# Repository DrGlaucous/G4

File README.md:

# "Governor" G4

This is a repo for a low-cost and feature-rich "flywheel-type" nerf blaster.

Features/Speficications:
- Goal build cost < 150$
- Minimal plastic-anchored screws *(almost evertthing is secured with bolts + captive nuts)*
- Brushless motor flyhweels
- Solenoid pusher
- LCD display
- Angled talon compatability *(straight stick support planned)*
- Integrated ammo counter hardware
- Integrated chronograph hardware
- 3-5S Lipo compatable
- 6cm flywheel diameter
- ESP32 controller
- Closed-loop flywheel control (providing fixed RPM and fast spinup times)
- Through-hole electronics and soldering
- Fast decay solenoid driver

Many of these features are implemented in the G4's companion firmware, [Detty](https://github.com/DrGlaucous/DettyFW).

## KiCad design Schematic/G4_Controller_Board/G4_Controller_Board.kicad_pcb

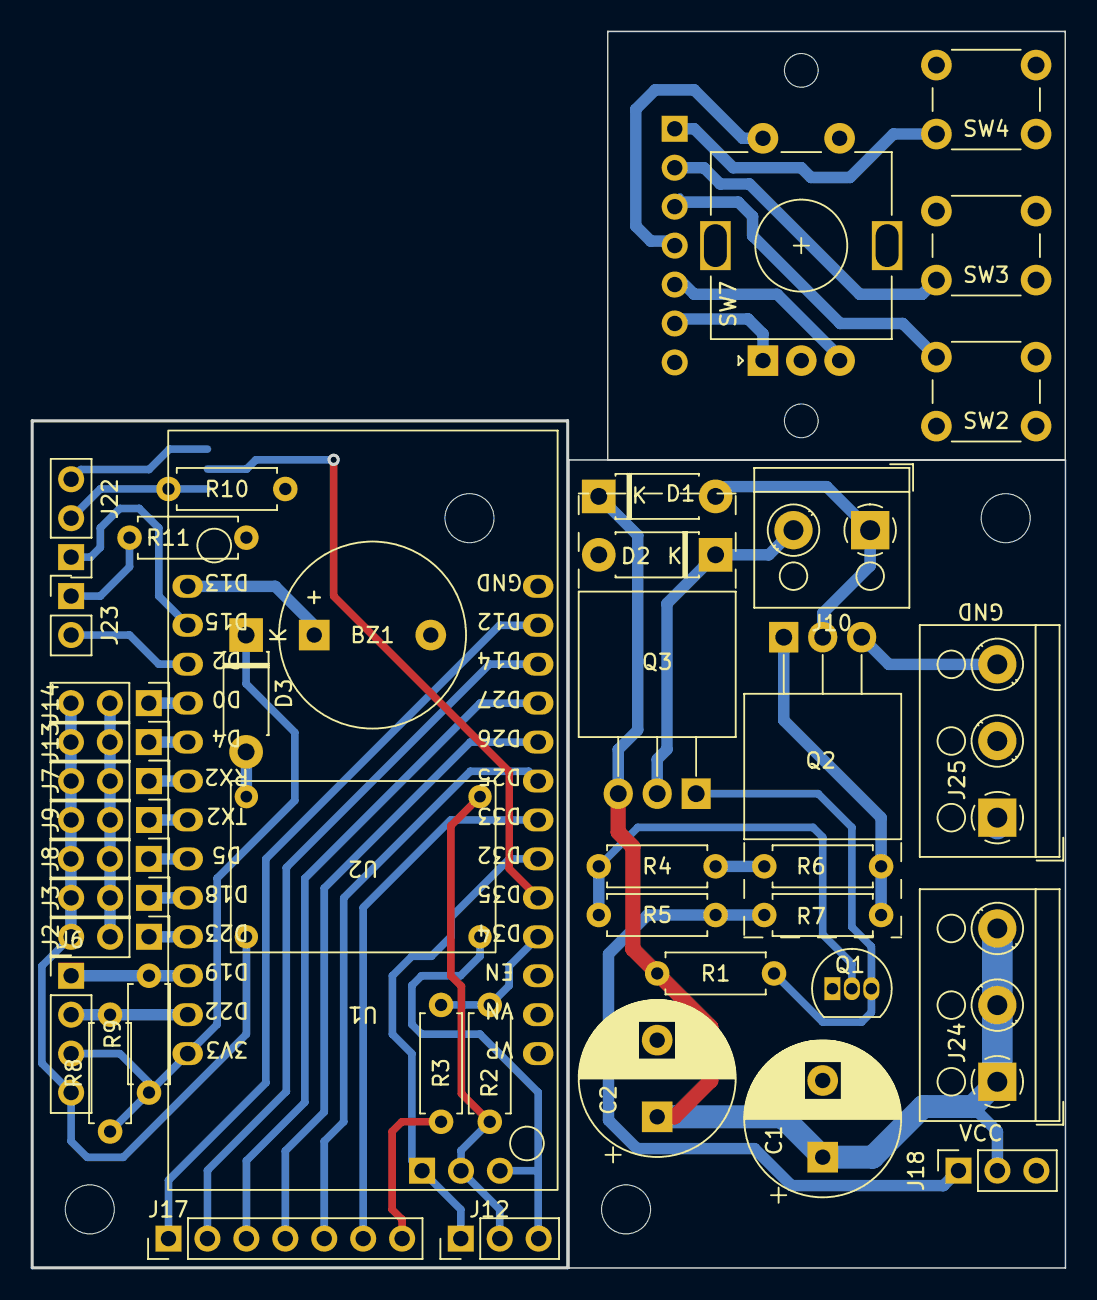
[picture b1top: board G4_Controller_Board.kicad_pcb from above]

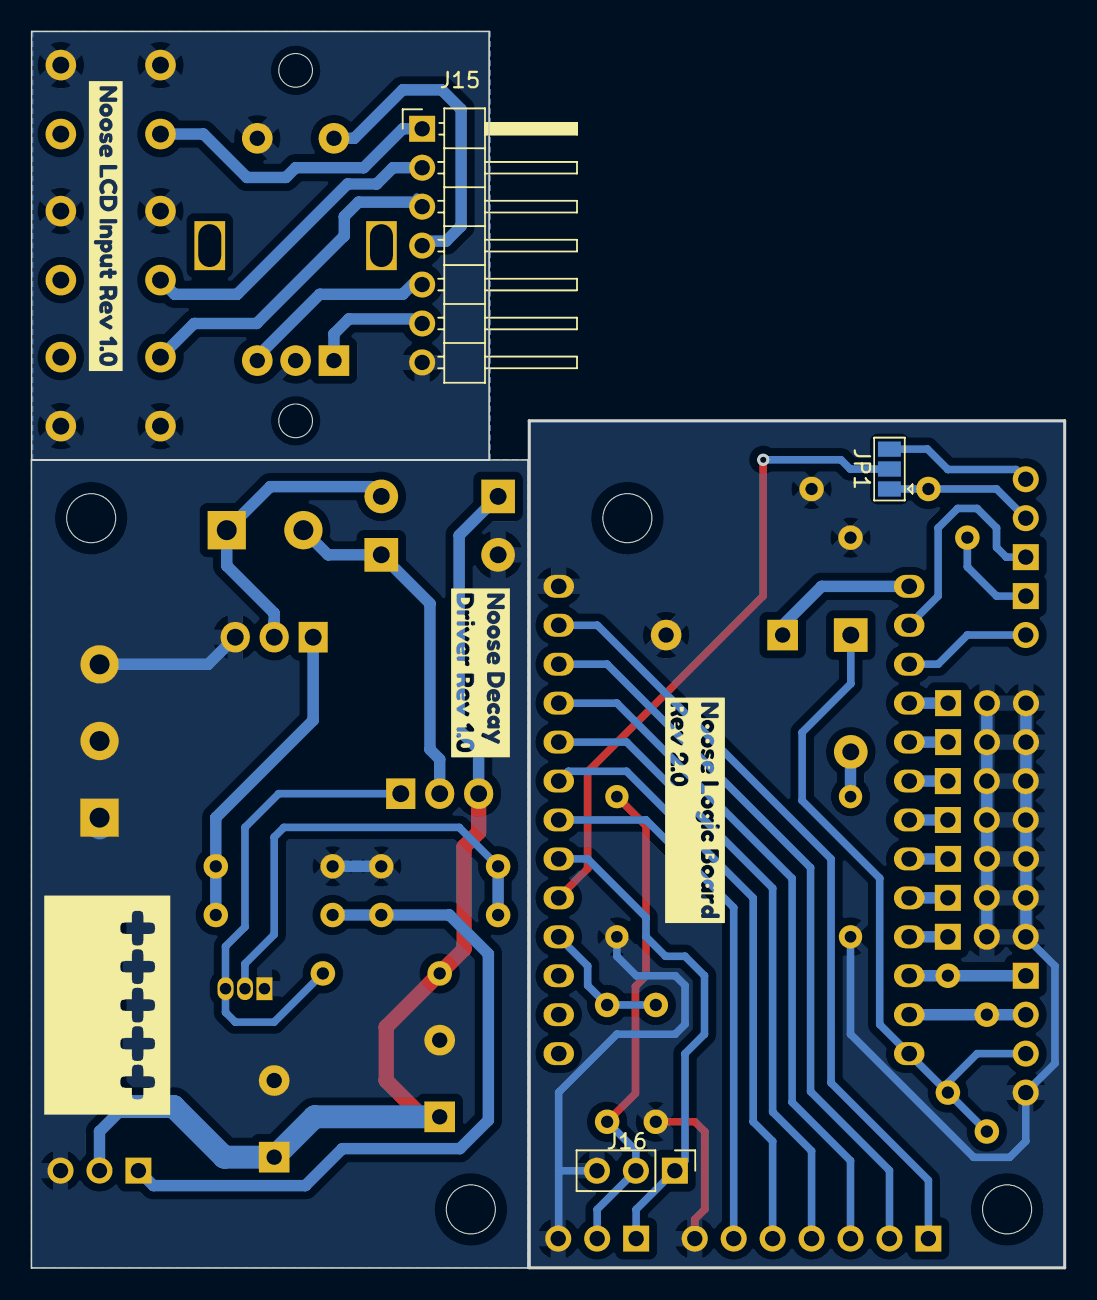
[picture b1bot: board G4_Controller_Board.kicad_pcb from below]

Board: 2 copper layers, 67.3 x 80.6 mm, 55 parts (7 on the bottom side), 33 nets.

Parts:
BZ1: Buzzer; Buzzer_12x9.5RM7.6
C1, C2: 470uF; CP_Radial_D10.0mm_P5.00mm
D1, D2, D3: 1N4001; D_DO-41_SOD81_P7.62mm_Horizontal
H1, H1#2, H1#3, H1#4: MountingHole; MountingHole_3.2mm_M3
H1#5, H1#6: MountingHole; MountingHole_2.2mm_M2
J2: ESC Right; PinHeader_1x03_P2.54mm_Vertical
J3: ESC Left; PinHeader_1x03_P2.54mm_Vertical
J6: I2C Out; PinHeader_1x04_P2.54mm_Vertical
J7: Rev Trigger (Optional); PinHeader_1x03_P2.54mm_Vertical
J8: Fire Trigger; PinHeader_1x03_P2.54mm_Vertical
J9: Magazine Removal Trigger; PinHeader_1x03_P2.54mm_Vertical
J10: Solenoid; TerminalBlock_RND_205-00001_1x02_P5.00mm_Horizontal
J12, J16: Board Interconnect; PinHeader_1x03_P2.54mm_Vertical
J13: SolenoidTrig A (Optional); PinHeader_1x03_P2.54mm_Vertical
J14: SolenoidTrig B (Optional); PinHeader_1x03_P2.54mm_Vertical
J15: Board Interconnect; PinHeader_1x07_P2.54mm_Horizontal
J17: Board Interconnect; PinHeader_1x07_P2.54mm_Vertical
J18: Board Interconnect; PinSocket_1x03_P2.54mm_Vertical
J22: IR LED Rec.; PinHeader_1x03_P2.54mm_Vertical
J23: IR LED Emitter; PinHeader_1x02_P2.54mm_Vertical
J24: Positive BUS; TerminalBlock_RND_205-00002_1x03_P5.00mm_Horizontal
J25: Negative BUS; TerminalBlock_RND_205-00002_1x03_P5.00mm_Horizontal
JP1: Jumper_3_Bridged12; SolderJumper-3_P1.3mm_Open_Pad1.0x1.5mm
Q1: 2N7000; TO-92_Inline
Q2: Q_NMOS_GDS; TO-220-3_Horizontal_TabUp
Q3: Q_PMOS_GDS; TO-220-3_Horizontal_TabUp
R1, R4, R6: 10KR; R_Axial_DIN0207_L6.3mm_D2.5mm_P7.62mm_Horizontal
R2: 150k Ohm; R_Axial_DIN0207_L6.3mm_D2.5mm_P7.62mm_Horizontal
R3: 10k Ohm; R_Axial_DIN0207_L6.3mm_D2.5mm_P7.62mm_Horizontal
R5, R7: 100R; R_Axial_DIN0207_L6.3mm_D2.5mm_P7.62mm_Horizontal
R8, R9: 2.4k Ohm; R_Axial_DIN0207_L6.3mm_D2.5mm_P7.62mm_Horizontal
R10: 10K Ohm; R_Axial_DIN0207_L6.3mm_D2.5mm_P7.62mm_Horizontal
R11: 90 Ohm; R_Axial_DIN0207_L6.3mm_D2.5mm_P7.62mm_Horizontal
SW2: Preset A; SW_PUSH_6mm_H13mm
SW3: Preset B; SW_PUSH_6mm_H13mm
SW4: Preset C; SW_PUSH_6mm_H13mm
SW7: RotaryEncoder_Switch; RotaryEncoder_Alps_EC11E-Switch_Vertical_H20mm
U1: ESP32-LOLIN32-Lite
U2: Mini360
kibuzzard-654684EA: G***; kibuzzard-654684EA
kibuzzard-654685C2: G***; kibuzzard-654685C2
kibuzzard-654685F2: G***; kibuzzard-654685F2
kibuzzard-65468392: G***; kibuzzard-65468392

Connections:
+3V3: D3.1 (K), J6.3, R8.1, R9.1, U1.40 (3V3)
+12V: C1.1, C2.1, D1.1 (K), J12.2, J16.2, J18.2, J24.1, J24.2, J24.3, Q3.3 (S), R1.1, R2.2, U2.2 (IN)
/Battery Reader: R2.1, R3.2, U1.10 (D34)
/Buzzer: BZ1.1 (-), U1.20 (D13)
/ESC Left: J3.1, U1.35 (D18)
/ESC Right: J2.1, U1.36 (D23)
/Encoder A: J15.6, J17.6, SW7.A, U1.13 (D33)
/Encoder B: J15.5, J17.5, SW7.B, U1.14 (D25)
/Encoder Switch: J15.4, J17.4, SW7.S2, U1.15 (D26)
/FireTrg: J8.1, U1.34 (D5)
/High Side Driver: Q1.2 (G), R4.2, R5.1
/IR Emitter: J23.2, U1.22 (D2)
/IR Rec. Supply: J22.1, U1.21 (D15)
/IR Reciever: JP1.2 (C), U1.11 (D35)
/Low Side Driver: Q2.1 (G), R6.2, R7.1
/MagTrg: J9.1, U1.27 (TX2/D17)
/Preset A: J15.3, J17.3, SW2.2, U1.16 (D27)
/Preset B: J15.2, J17.2, SW3.1, U1.17 (D14)
/Preset C: J15.1, J17.1, SW4.1, U1.18 (D12)
/Pusher Pin: J12.1, J16.1, J18.1, R5.2, R7.2, U1.12 (D32)
/RevTrg: J7.1, U1.25 (RX2/D16)
/SCL/SCK (Clock): J6.2, R8.2, U1.39 (D22)
/SDA/SDI (Data): J6.1, R9.2, U1.38 (D19)
/SOLENOID_A: D1.2 (A), J10.1, Q2.2 (D)
/SOLENOID_B: D2.1 (K), J10.2, Q3.2 (D)
/SolTrig A: J13.1, U1.24 (D4)
/SolTrig B: J14.1, U1.23 (D0)
GND: BZ1.2 (+), C1.2, C2.2, D2.2 (A), J2.2, J2.3, J3.2, J3.3, J6.4, J7.2, J7.3, J8.2, J8.3, J9.2, J9.3, J12.3, J13.2, J13.3, J14.2, J14.3, J15.7, J16.3, J17.7, J18.3, J25.1, J25.2, J25.3, Q1.1 (S), Q2.3 (S), R3.1, R4.1, R6.1, R10.1, R11.1, SW2.1, SW3.2, SW4.2, SW7.C, SW7.S1, U1.19 (GND), U2.1 (GND), U2.3 (GND)
unnamed: D3.2 (A), U2.4 (OUT)
unnamed: J22.2, JP1.1 (A), R10.2
unnamed: J22.3, JP1.3 (B)
unnamed: J23.1, R11.2
unnamed: Q1.3 (D), Q3.1 (G), R1.2

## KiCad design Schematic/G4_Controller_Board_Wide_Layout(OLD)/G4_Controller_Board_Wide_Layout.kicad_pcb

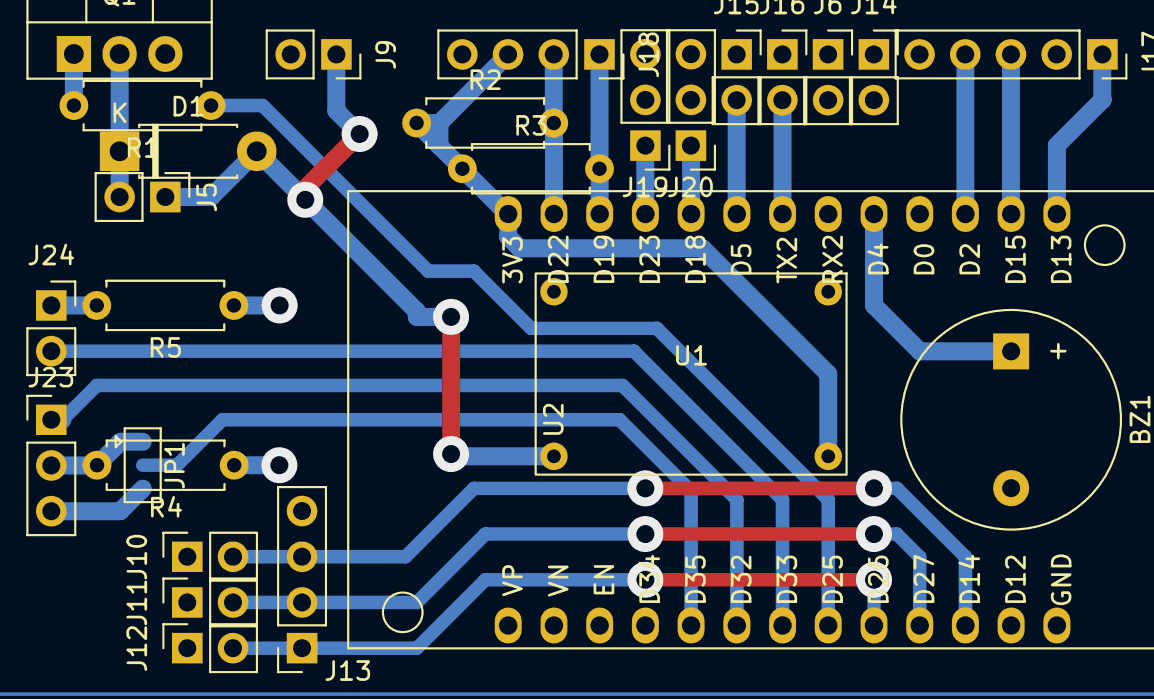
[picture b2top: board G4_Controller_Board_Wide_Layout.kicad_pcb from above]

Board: 2 copper layers, 27 parts (0 on the bottom side), 25 nets.

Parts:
BZ1: Buzzer; Buzzer_12x9.5RM7.6
D1: IN4001; D_DO-41_SOD81_P7.62mm_Horizontal
J5: Solenoid; PinHeader_1x02_P2.54mm_Vertical
J6, J15: Fire Trigger; PinSocket_1x02_P2.54mm_Vertical
J9: 12 Volts In; PinSocket_1x02_P2.54mm_Vertical
J10: Preset A; PinSocket_1x02_P2.54mm_Vertical
J11: Preset B; PinSocket_1x02_P2.54mm_Vertical
J12: Preset C; PinSocket_1x02_P2.54mm_Vertical
J13: Combined Preset Connector; PinSocket_1x04_P2.54mm_Vertical
J14: Rev Trigger (Optional); PinSocket_1x02_P2.54mm_Vertical
J16: Magazine Removal Trigger; PinSocket_1x02_P2.54mm_Vertical
J17: Rotary Encoder; PinSocket_1x05_P2.54mm_Vertical
J18: I2C Out; PinSocket_1x04_P2.54mm_Vertical
J19: ESC Right; PinHeader_1x03_P2.54mm_Vertical
J20: ESC Left; PinHeader_1x03_P2.54mm_Vertical
J23: IR LED Rec.; PinHeader_1x03_P2.54mm_Vertical
J24: IR LED Emitter; PinSocket_1x02_P2.54mm_Vertical
JP1: Jumper_3_Bridged12; SolderJumper-3_P1.3mm_Open_Pad1.0x1.5mm
Q1: IRF540N; TO-220-3_Vertical
R1: 220; R_Axial_DIN0207_L6.3mm_D2.5mm_P7.62mm_Horizontal
R2, R3: 2.4k Ohm; R_Axial_DIN0207_L6.3mm_D2.5mm_P7.62mm_Horizontal
R4: 10K Ohm; R_Axial_DIN0207_L6.3mm_D2.5mm_P7.62mm_Horizontal
R5: 90 Ohm; R_Axial_DIN0207_L6.3mm_D2.5mm_P7.62mm_Horizontal
U1: Mini360
U2: ESP32-LOLIN32-Lite

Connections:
+3V3: J18.3, R2.1, R3.1, U1.4 (OUT), U2.40 (3V3)
+12V: D1.2 (A), J5.1, J9.1, U1.2 (IN)
/Buzzer: BZ1.1 (-), U2.24 (D4)
/ESC Left: J20.1, U2.35 (D18)
/ESC Right: J19.1, U2.36 (D23)
/Encoder A: J17.4, U2.22 (D2)
/Encoder B: J17.3, U2.21 (D15)
/Encoder Switch: J17.1, U2.20 (D13)
/FireTrg: J15.2, U2.34 (D5)
/IR Emitter: J24.2, U2.13 (D33)
/IR Rec. Supply: J23.1, U2.12 (D32)
/IR Reciever: JP1.2 (C), U2.11 (D35)
/MagTrg: J16.2, U2.27 (TX2)
/PUSHER PIN: R1.1, U2.14 (D25)
/Preset A: J10.2, J13.3, U2.17 (D14)
/Preset B: J11.2, J13.2, U2.16 (D27)
/Preset C: J12.2, J13.1, U2.15 (D26)
/SCL/SCK (Clock): J18.2, R2.2, U2.39 (D22)
/SDA/SDI (Data): J18.1, R3.2, U2.38 (D19)
GND: BZ1.2 (+), J9.2, J10.1, J11.1, J12.1, J13.4, J14.1, J15.1, J16.1, J17.2, J17.5, J18.4, J19.3, J20.3, Q1.3 (S), R4.1, R5.1, U1.1 (GND), U1.3 (GND), U2.19 (GND)
unnamed: D1.1 (K), J5.2, Q1.2 (D)
unnamed: J23.2, JP1.1 (A), R4.2
unnamed: J23.3, JP1.3 (B)
unnamed: J24.1, R5.2
unnamed: Q1.1 (G), R1.2

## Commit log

2023-06-04 CAD -woot woot
    I think I know what it's going to look like...
2023-06-05 more cad work, added ESC music
    simple as that.
2023-06-10 basic blaster is almost done
    currently, it's a box, but a functional box...
2023-06-14 CAD updates
    Added screw holes to everything...
2023-06-20 Lots of CAD
2023-06-21 heavy cad work
2023-06-23 more CAD work, very close to finished product
    I failed to meet the deadline, but I came darn close
2023-06-23 created the G4 PCB
    all of it.
2023-07-11 working on software
    ported FDL3 software to platformIO (for reference only)
2023-07-11 CAD
    exported to STL for printing, made some model tweaks as problems were found
2023-07-22 Programming work
    Trying to get d-shot bidirectional working on an ESP32
2023-08-09 firmware updates
    started work on "detty"
2023-08-10 some minor additions
    updated flywheels.h
2023-08-14 updated controller board schematics
2023-08-21 work on Detty
    working with menu UI
2023-08-22 UI work
    integrating menus and gauges into the firmware
2023-08-23 working with the draw code
    had to add a timed interrupt in order to update the input quickly enough in light of the u8g2 code
2023-08-26 implement basic menu
    used the GEM-Breakout library and fixed some other bugs
2023-08-28 more display functionality
    created basic display layout plan
2023-08-29 more firmware work
    began work on settings
2023-09-01 a few small changes to firmware
    mostly just some work on the settings (such that it is)
2023-09-05 begin work on connectome
    fixed flywheel and solenoid backends
2023-09-07 more firmware updates
    select fire and cache behavior created
2023-09-08 add basic full auto
    currently does not acknowledge trigger type
2023-09-14 firmware and hardware revisions
    need to beef up flywheels and redesign electronics bay
2023-09-28 CAD updates
    working on new flywheel cage design
2023-09-29 CAD updates
2023-10-12 update CAD
2023-10-15 work on newer board revision
    spitting into 2 boards to make the design both more compact and robust
2023-10-17 begin work on new PCB
    2 layers with fast decay driver
2023-10-17 update the PCB
    added more traces
2023-10-19 update PCB model
    progress on logic-side board
2023-10-20 update kicad schematic
2023-10-23 try 3 flywheel mount
    tried single piece flywheel mount, but that resulted in print issues, so I'm trying a different method that uses more bolts. Also updated other things such as the PCB.
2023-10-23 more work on front cage (small work)
2023-10-28 update PCB
    prototype revision should be completed
2023-10-31 Last save of 2 board setup
    current boards integrate half-bridge and IO buttons on the same PCB, with the ESP32 on the other one. I'm considering splitting the encoder and buttons off into their own floating PCB, leaving more r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
2023-11-02 update PCB
    trying 3 PCB config (floating buttons, ESP32, and fast decay driver)
2023-11-02 add updated CAD files
    oops, this should have been with the last commit!
2023-11-03 update PCB traces
2023-11-05 create machine code for PCB
    nc code generated to machine out the physical PCB tests
2023-11-05 rename folder
2023-11-06 CAD and CNC updates
2023-11-09 CAD updates
    add models of controller board to SKP
2023-11-10 decay driver test code and updated CAD
    what it says on the tin
2023-11-11 shift files
2023-11-22 CAD updates
    approaching finished product
2023-11-23 work on firmware
    attempting to add task scheduling and chronometer
2023-11-27 firmware upsates
    add more support for ammo counter, still not working
2024-01-16 split Detty into 2 sub-types
    synchro-detty doesn't use task scheduling, while async-detty does
2024-01-21 !Statistics!
    How fun
2024-08-29 notes and old changes
    these have been sitting around for a bit, but I haven't pushed it for some reason
2024-08-29 split detty into its own repository
2024-08-29 Update readme info
2024-12-13 tests for g4 firmware
